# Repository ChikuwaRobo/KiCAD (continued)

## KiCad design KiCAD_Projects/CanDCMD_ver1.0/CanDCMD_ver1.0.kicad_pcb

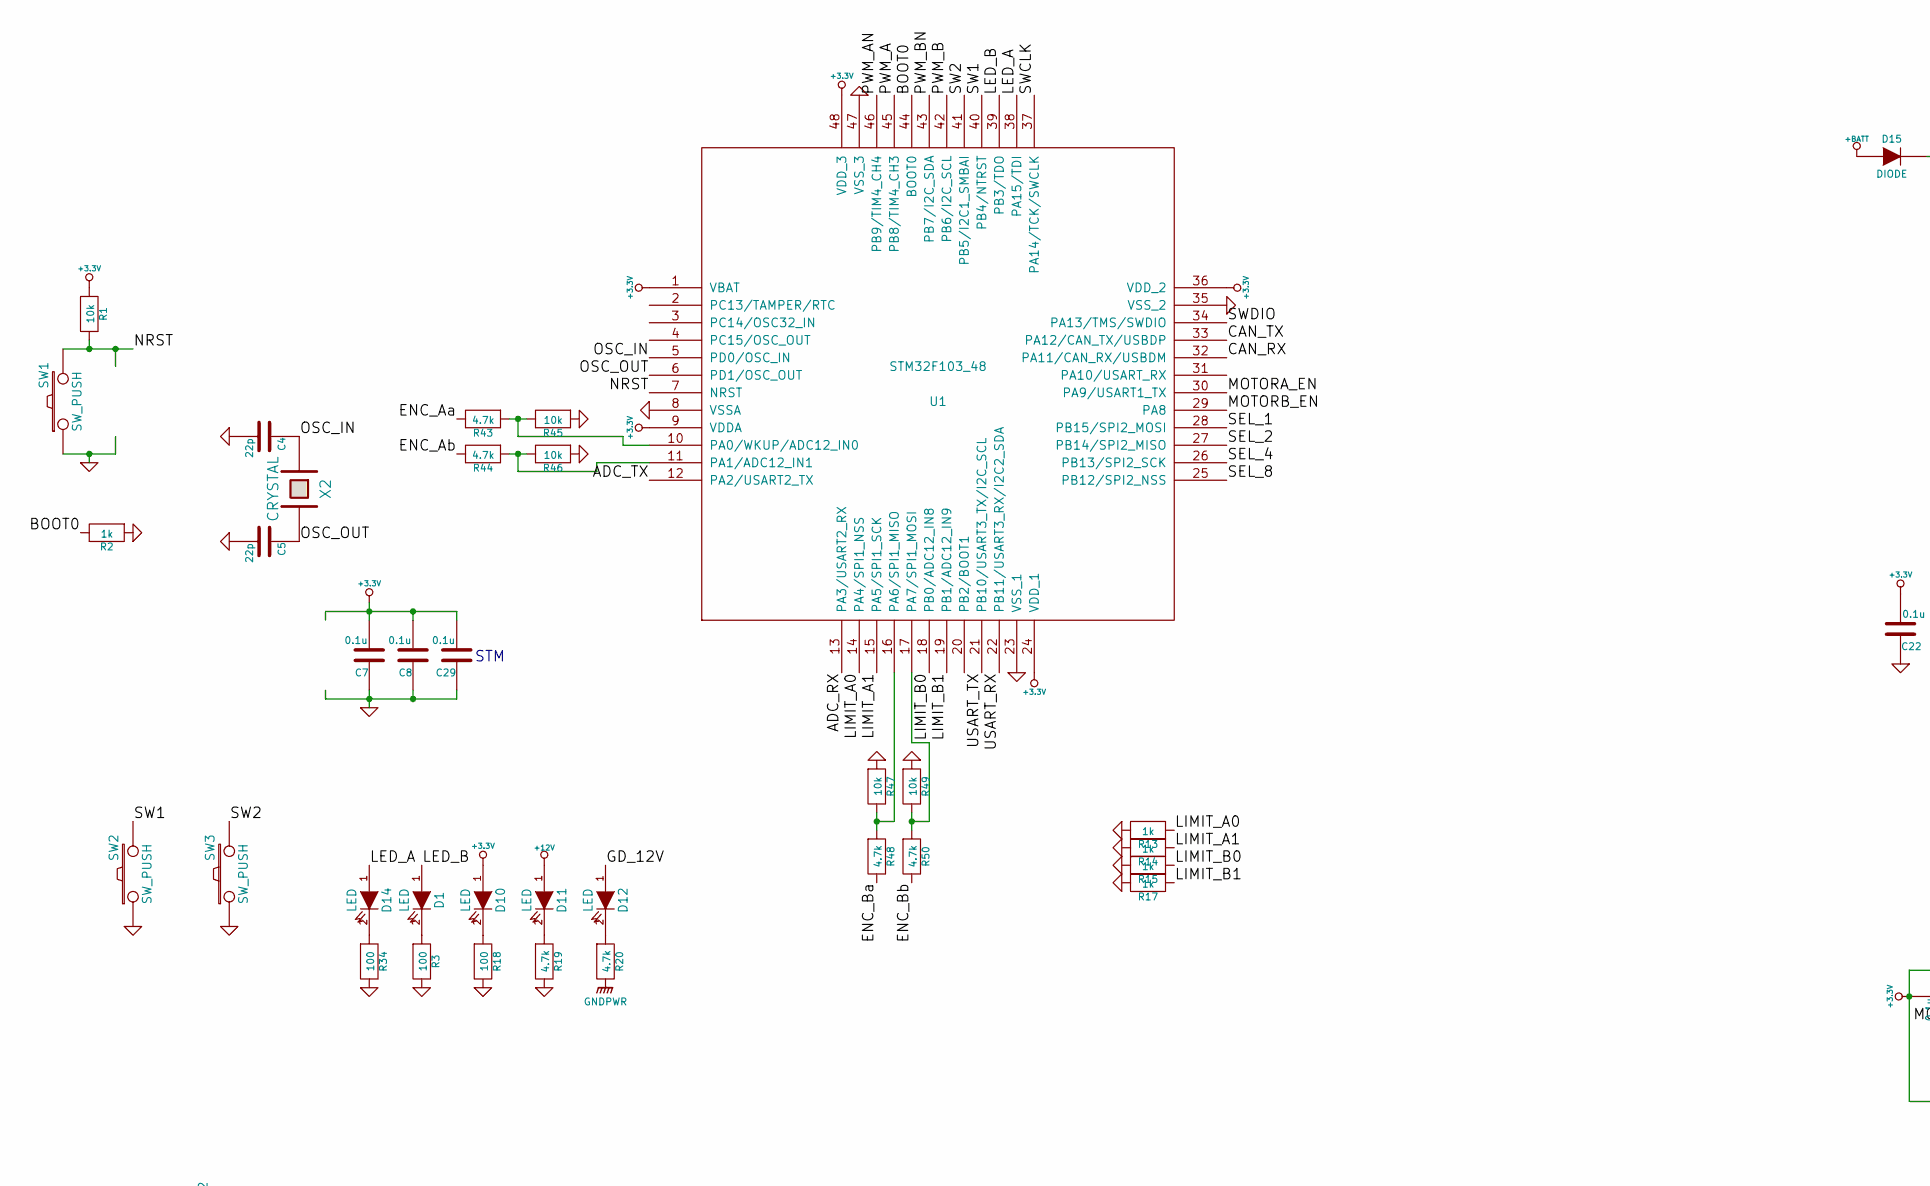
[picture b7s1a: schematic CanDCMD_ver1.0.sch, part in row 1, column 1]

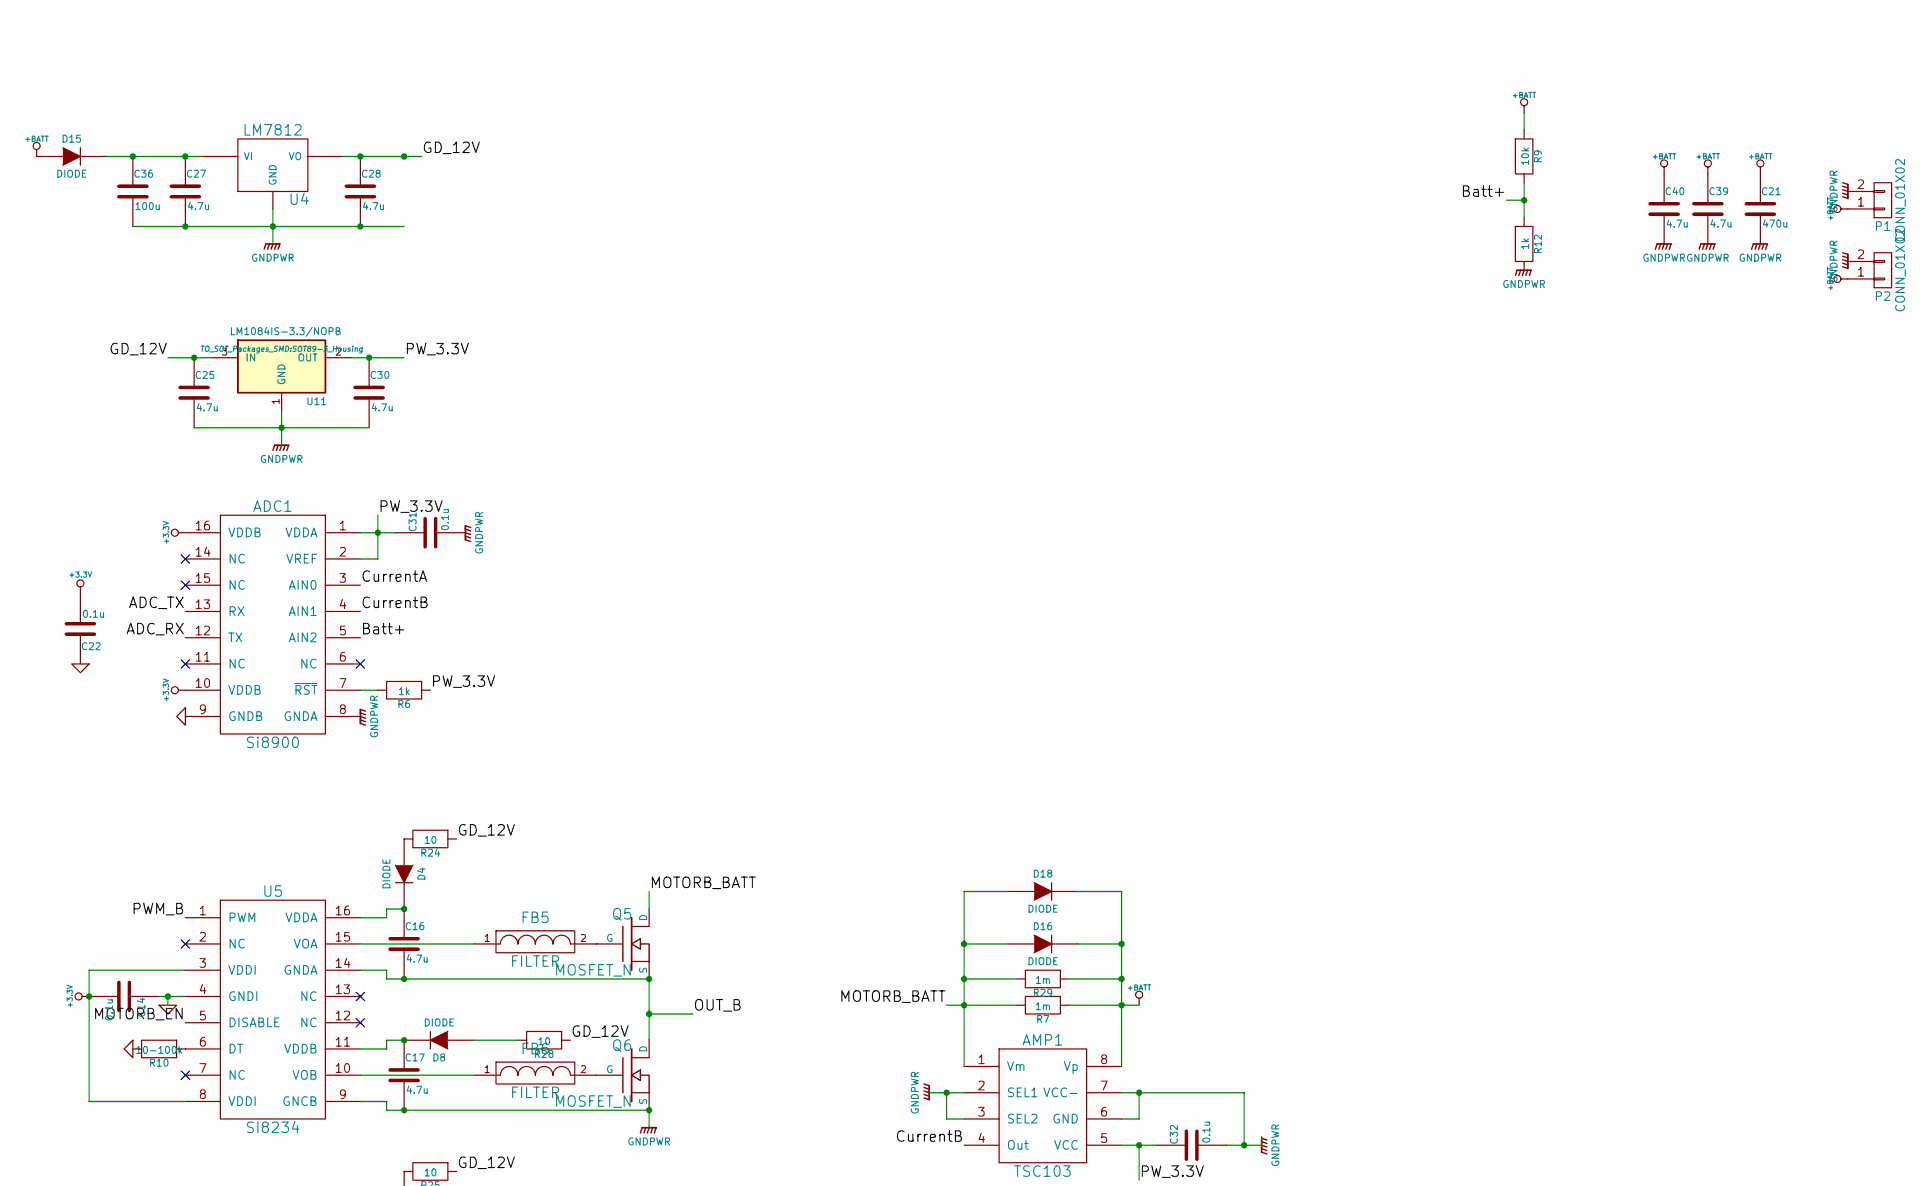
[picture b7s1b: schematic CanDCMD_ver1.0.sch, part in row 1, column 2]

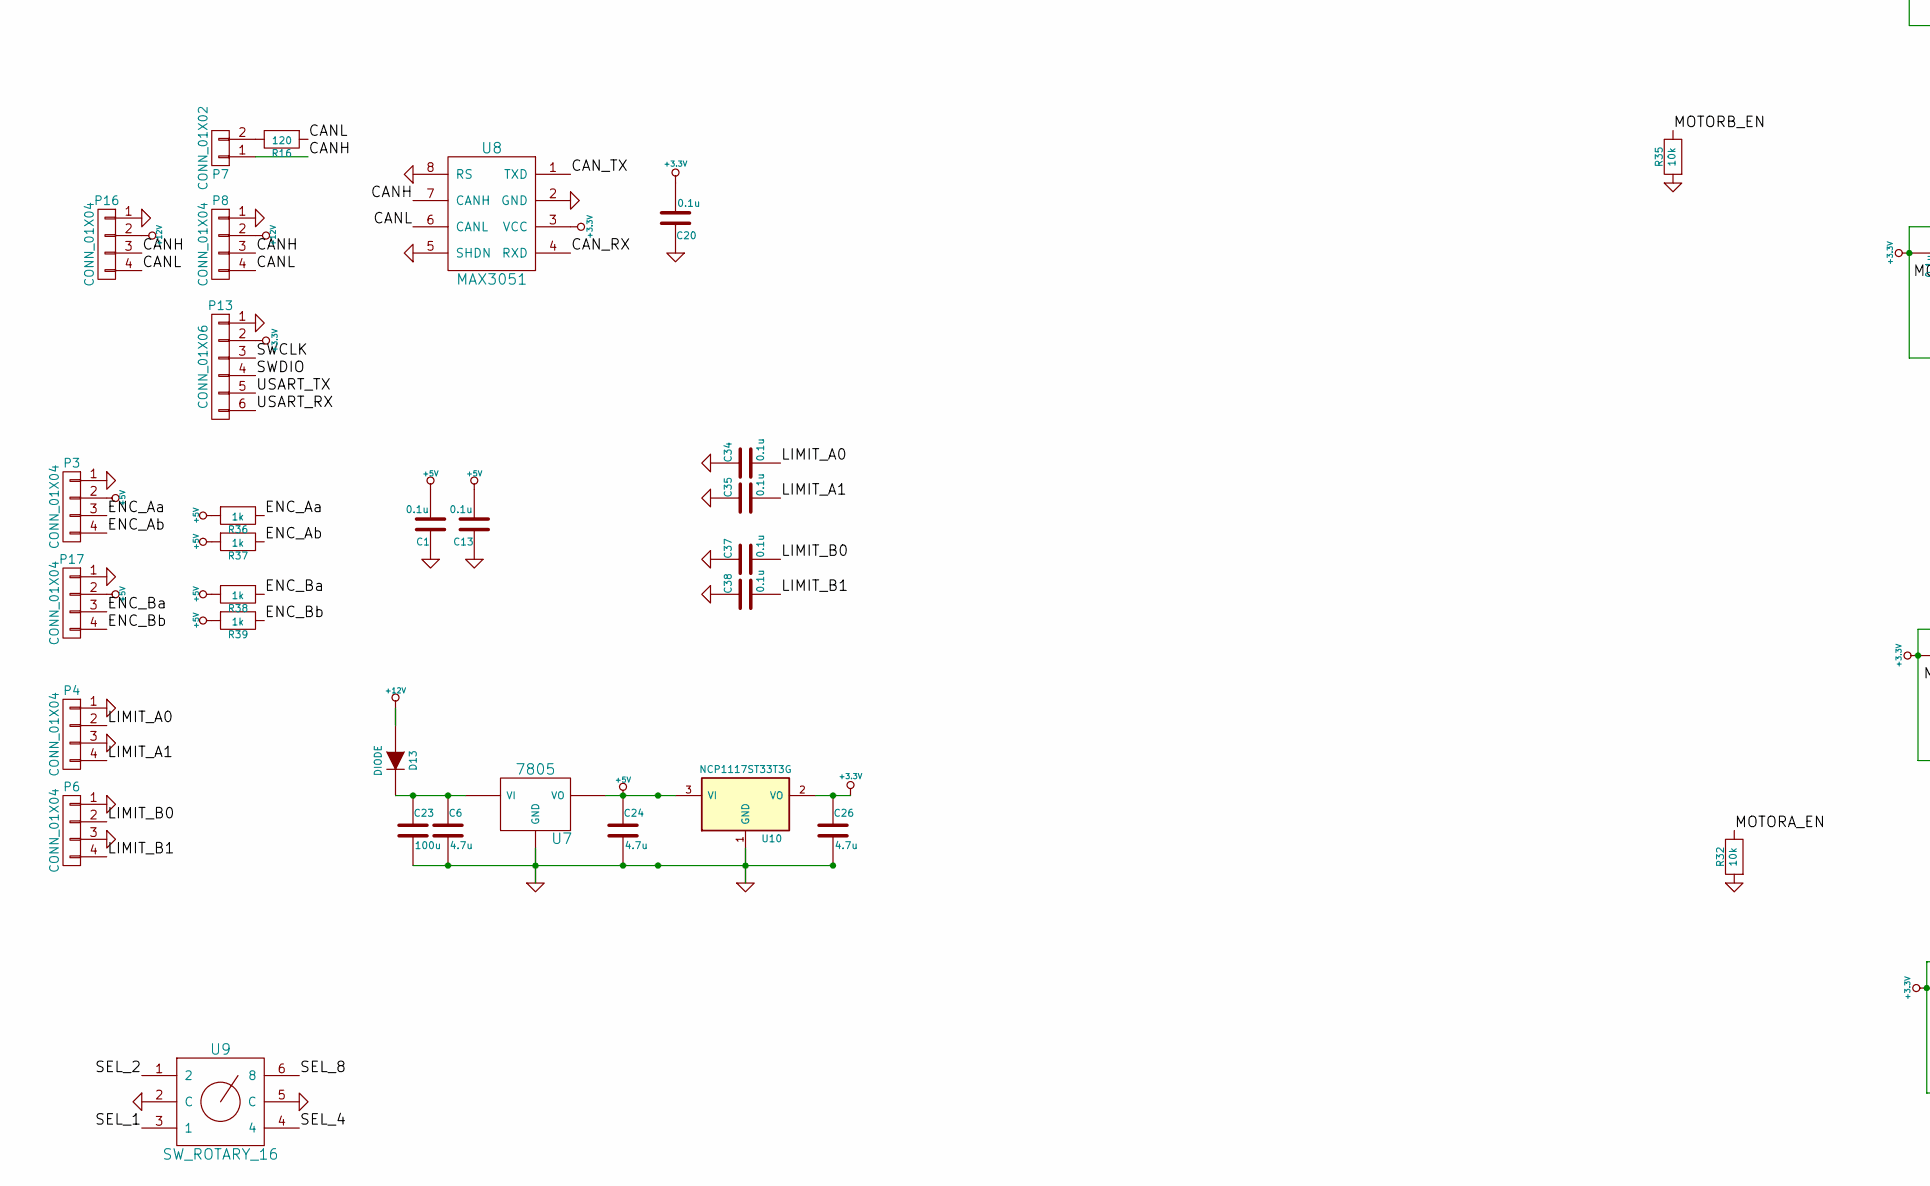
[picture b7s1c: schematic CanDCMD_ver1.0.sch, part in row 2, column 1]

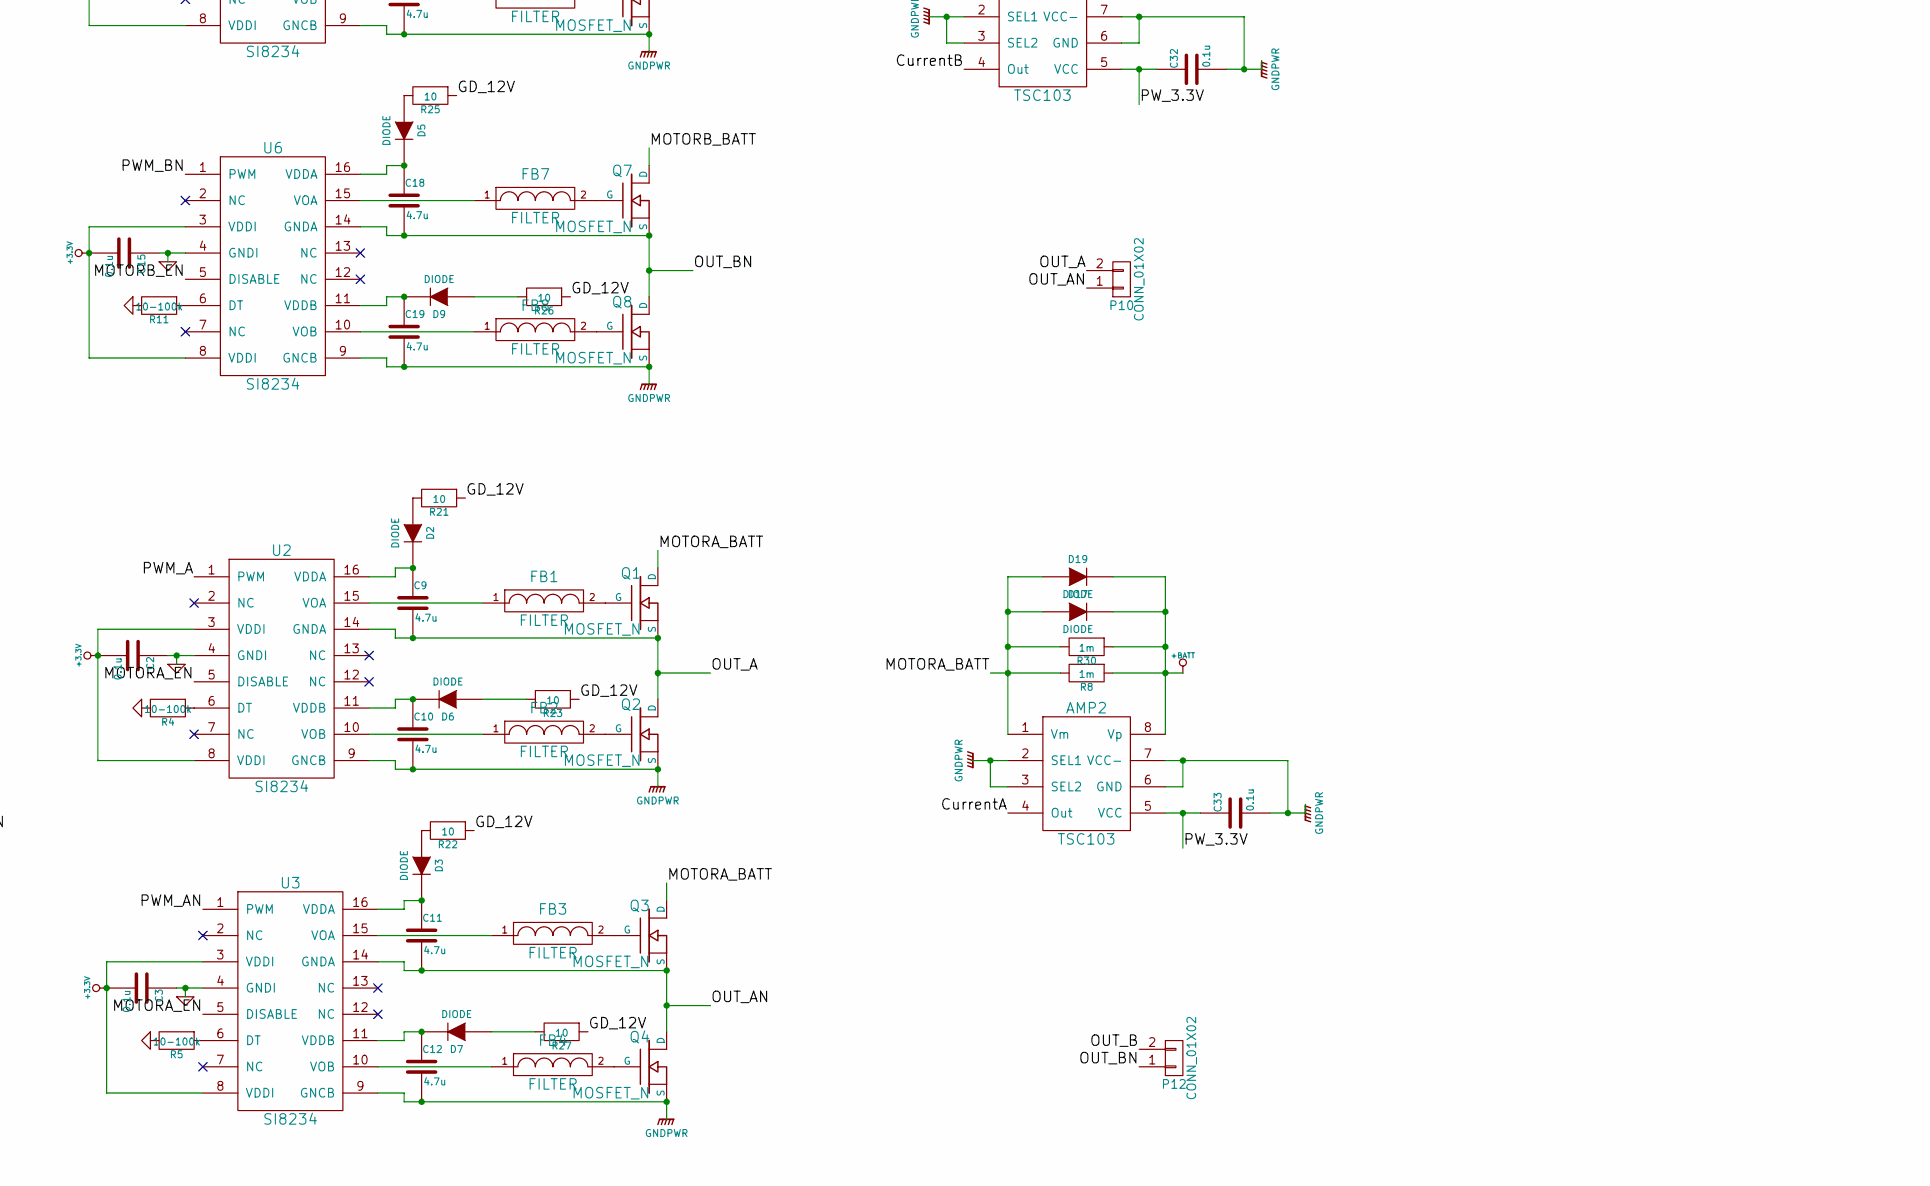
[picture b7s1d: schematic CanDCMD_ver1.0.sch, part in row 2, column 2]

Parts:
ADC1: Si8900; SOIC-16_7.5x10.3mm_Pitch1.27mm
AMP1, AMP2: TSC103; SOIC-8_3.9x4.9mm_Pitch1.27mm
C1, C2, C3, C7, C8, C13, C14, C15, C20, C22, C29, C31, C32, C33, C34, C35, C37, C38: 0.1u; C1608_WP
C4, C5: 22p; C1608_WP
C6, C9, C10, C11, C12, C16, C17, C18, C19, C24, C25, C26, C27, C28, C30, C39, C40: 4.7u; C3216
C21: 470u; C_Radial_D12.5_L25_P5
C23, C36: 100u; C_Radial_D6.3_L11.2_P2.5
D1, D10, D11, D12, D14: LED; C1608_WP
D2, D3, D4, D5, D6, D7, D8, D9: DIODE; C1608_WP
D13, D15: DIODE; C3216
D16, D17, D18, D19: DIODE; POWER_DI5
FB1, FB2, FB3, FB4, FB5, FB6, FB7, FB8: FILTER; C1608_WP
P1: CONN_01X02; DEANS_T_M
P2: CONN_01X02; DEANS_T_F
P3, P4, P6, P8, P16, P17: CONN_01X04; XA_4LC
P7: CONN_01X02; Pin_Header_Straight_1x02
P10, P12: CONN_01X02; DEANS_T_F_minPad
P13: CONN_01X06; ZH_6T
Q1, Q2, Q3, Q4, Q5, Q6, Q7, Q8: MOSFET_N; D2-PAK_compact
R1, R9, R32, R35, R45, R46, R47, R49: 10k; C1608_WP
R2, R6, R12, R13, R14, R15, R17, R36, R37, R38, R39: 1k; C1608_WP
R3, R18, R34: 100; C1608_WP
R4, R5, R10, R11: 10-100k; C1608_WP
R7, R8, R29, R30: 1m; R5025
R16: 120; C1608_WP
R19, R20, R43, R44, R48, R50: 4.7k; C1608_WP
R21, R22, R23, R24, R25, R26, R27, R28: 10; C1608_WP
SW1, SW2, SW3: SW_PUSH; RP_SMD_Button
U1: STM32F103_48; LQFP-48_7x7mm_Pitch0.5mm
U2, U3, U5, U6: SI8234; SOIC-16_3.9x9.9mm_Pitch1.27mm
U4: LM7812; TO-252-2Lead_regu
U7: 7805; TO-252-2Lead_regu
U8: MAX3051; SOIC-8_3.9x4.9mm_Pitch1.27mm
U9: SW_ROTARY_16; rotary_0F
U10: NCP1117ST33T3G; SOT-223_reg
U11: LM1084IS-3.3/NOPB; SOT89-3_Housing
X2: CRYSTAL; ABM3_2pads

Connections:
+3.3V: ADC1.10 (VDDB), ADC1.16 (VDDB), C2.2, C3.2, C7.2, C8.2, C14.2, C15.2, C20.2, C22.2, C26.1, C29.2, D10.1 (A), P13.2, R1.1, U1.1 (VBAT), U1.9 (VDDA), U1.24 (VDD_1), U1.36 (VDD_2), U1.48 (VDD_3), U2.3 (VDDI), U2.8 (VDDI), U3.3 (VDDI), U3.8 (VDDI), U5.3 (VDDI), U5.8 (VDDI), U6.3 (VDDI), U6.8 (VDDI), U8.3 (VCC), U10.2 (VO)
+5V: C1.2, C13.2, C24.1, P3.2, P17.2, R36.1, R37.1, R38.1, R39.1, U7.VO, U10.3 (VI)
+12V: D11.1 (A), D13.1 (A), P8.2, P16.2
+BATT: AMP1.8 (Vp), AMP2.8 (Vp), C21.1, C39.1, C40.1, D15.1 (A), D16.1 (K), D17.1 (K), D18.1 (K), D19.1 (K), P1.1, P2.1, R7.1, R8.1, R9.1, R29.1, R30.1
/ADC_RX: ADC1.12 (TX), U1.13 (PA3/USART2_RX)
/ADC_TX: ADC1.13 (RX), U1.12 (PA2/USART2_TX)
/BOOT0: R2.2, U1.44 (BOOT0)
/Batt+: ADC1.5 (AIN2), R9.2, R12.1
/CANH: P7.1, P8.3, P16.3, U8.7 (CANH)
/CANL: P8.4, P16.4, R16.1, U8.6 (CANL)
/CAN_RX: U1.32 (PA11/CAN_RX/USBDM), U8.4 (RXD)
/CAN_TX: U1.33 (PA12/CAN_TX/USBDP), U8.1 (TXD)
/CurrentA: ADC1.3 (AIN0), AMP2.4 (Out)
/CurrentB: ADC1.4 (AIN1), AMP1.4 (Out)
/ENC_Aa: P3.3, R36.2, R43.2
/ENC_Ab: P3.4, R37.2, R44.2
/ENC_Ba: P17.3, R38.2, R48.2
/ENC_Bb: P17.4, R39.2, R50.2
/GD_12V: C25.1, C28.1, D12.1 (A), R21.1, R22.1, R23.1, R24.1, R25.1, R26.1, R27.1, R28.1, U4.VO, U11.3 (IN)
/LED_A: D14.1 (A), U1.38 (PA15/TDI)
/LED_B: D1.1 (A), U1.39 (PB3/TDO)
/LIMIT_A0: C34.2, P4.2, R13.1, U1.14 (PA4/SPI1_NSS)
/LIMIT_A1: C35.2, P4.4, R14.1, U1.15 (PA5/SPI1_SCK)
/LIMIT_B0: C37.2, P6.2, R15.1, U1.18 (PB0/ADC12_IN8)
/LIMIT_B1: C38.2, P6.4, R17.1, U1.19 (PB1/ADC12_IN9)
/MOTORA_BATT: AMP2.1 (Vm), D17.2 (A), D19.2 (A), Q1.D, Q3.D, R8.2, R30.2
/MOTORA_EN: R32.2, U1.30 (PA9/USART1_TX), U2.5 (DISABLE), U3.5 (DISABLE)
/MOTORB_BATT: AMP1.1 (Vm), D16.2 (A), D18.2 (A), Q5.D, Q7.D, R7.2, R29.2
/MOTORB_EN: R35.2, U1.29 (PA8), U5.5 (DISABLE), U6.5 (DISABLE)
/NRST: R1.2, SW1.2, U1.7 (NRST)
/OSC_IN: C4.1, U1.5 (PD0/OSC_IN), X2.1
/OSC_OUT: C5.1, U1.6 (PD1/OSC_OUT), X2.2
/OUT_A: C9.2, P10.2, Q1.S, Q2.D, U2.14 (GNDA)
/OUT_AN: C11.2, P10.1, Q3.S, Q4.D, U3.14 (GNDA)
/OUT_B: C16.2, P12.2, Q5.S, Q6.D, U5.14 (GNDA)
/OUT_BN: C18.2, P12.1, Q7.S, Q8.D, U6.14 (GNDA)
/PWM_A: U1.45 (PB8/TIM4_CH3), U2.1 (PWM)
/PWM_AN: U1.46 (PB9/TIM4_CH4), U3.1 (PWM)
/PWM_B: U1.42 (PB6/I2C_SCL), U5.1 (PWM)
/PWM_BN: U1.43 (PB7/I2C_SDA), U6.1 (PWM)
/PW_3.3V: ADC1.1 (VDDA), ADC1.2 (VREF), AMP1.5 (VCC), AMP2.5 (VCC), C30.1, C31.1, C32.1, C33.1, R6.1, U11.2 (OUT)
/SEL_1: U1.28 (PB15/SPI2_MOSI), U9.3 (1)
/SEL_2: U1.27 (PB14/SPI2_MISO), U9.1 (2)
/SEL_4: U1.26 (PB13/SPI2_SCK), U9.4
/SEL_8: U1.25 (PB12/SPI2_NSS), U9.6 (8)
/SW1: SW2.2, U1.40 (PB4/NTRST)
/SW2: SW3.2, U1.41 (PB5/I2C1_SMBAI)
/SWCLK: P13.3, U1.37 (PA14/TCK/SWCLK)
/SWDIO: P13.4, U1.34 (PA13/TMS/SWDIO)
/USART_RX: P13.6, U1.22 (PB11/USART3_RX/I2C2_SDA)
/USART_TX: P13.5, U1.21 (PB10/USART3_TX/I2C_SCL)
GND: ADC1.9 (GNDB), C1.1, C2.1, C3.1, C4.2, C5.2, C6.2, C7.1, C8.1, C13.1, C14.1, C15.1, C20.1, C22.1, C23.2, C24.2, C26.2, C29.1, C34.1, C35.1, C37.1, C38.1, P3.1, P4.1, P4.3, P6.1, P6.3, P8.1, P13.1, P16.1, P17.1, R2.1, R3.2, R4.2, R5.2, R10.2, R11.2, R13.2, R14.2, R15.2, R17.2, R18.2, R19.2, R32.1, R34.2, R35.1, R45.1, R46.1, R47.1, R49.1, SW1.1, SW2.1, SW3.1, U1.8 (VSSA), U1.23 (VSS_1), U1.35 (VSS_2), U1.47 (VSS_3), U2.4 (GNDI), U3.4 (GNDI), U5.4 (GNDI), U6.4 (GNDI), U7.GND, U8.2 (GND), U8.5 (SHDN), U8.8 (RS), U9.2 (C), U9.5 (C), U10.1 (GND)
GNDPWR: ADC1.8 (GNDA), AMP1.2 (SEL1), AMP1.3 (SEL2), AMP1.6 (GND), AMP1.7 (VCC-), AMP2.2 (SEL1), AMP2.3 (SEL2), AMP2.6 (GND), AMP2.7 (VCC-), C10.2, C12.2, C17.2, C19.2, C21.2, C25.2, C27.2, C28.2, C30.2, C31.2, C32.2, C33.2, C36.2, C39.2, C40.2, P1.2, P2.2, Q2.S, Q4.S, Q6.S, Q8.S, R12.2, R20.2, U2.9 (GNCB), U3.9 (GNCB), U4.GND, U5.9 (GNCB), U6.9 (GNCB), U11.1 (GND)
unnamed: ADC1.7 (~RST), R6.2
unnamed: C9.1, D2.2 (K), U2.16 (VDDA)
unnamed: C10.1, D6.2 (K), U2.11 (VDDB)
unnamed: C11.1, D3.2 (K), U3.16 (VDDA)
unnamed: C12.1, D7.2 (K), U3.11 (VDDB)
unnamed: C16.1, D4.2 (K), U5.16 (VDDA)
unnamed: C17.1, D8.2 (K), U5.11 (VDDB)
unnamed: C18.1, D5.2 (K), U6.16 (VDDA)
unnamed: C19.1, D9.2 (K), U6.11 (VDDB)
unnamed: C6.1, C23.1, D13.2 (K), U7.VI
unnamed: C27.1, C36.1, D15.2 (K), U4.VI
unnamed: D1.2 (K), R3.1
unnamed: D2.1 (A), R21.2
unnamed: D3.1 (A), R22.2
unnamed: D4.1 (A), R24.2
unnamed: D5.1 (A), R25.2
unnamed: D6.1 (A), R23.2
unnamed: D7.1 (A), R27.2
unnamed: D8.1 (A), R28.2
unnamed: D9.1 (A), R26.2
unnamed: D10.2 (K), R18.1
unnamed: D11.2 (K), R19.1
unnamed: D12.2 (K), R20.1
unnamed: D14.2 (K), R34.1
unnamed: FB1.1, U2.15 (VOA)
unnamed: FB1.2, Q1.G
unnamed: FB2.1, U2.10 (VOB)
unnamed: FB2.2, Q2.G
unnamed: FB3.1, U3.15 (VOA)
unnamed: FB3.2, Q3.G
unnamed: FB4.1, U3.10 (VOB)
unnamed: FB4.2, Q4.G
unnamed: FB5.1, U5.15 (VOA)
unnamed: FB5.2, Q5.G
unnamed: FB6.1, U5.10 (VOB)
unnamed: FB6.2, Q6.G
unnamed: FB7.1, U6.15 (VOA)
unnamed: FB7.2, Q7.G
unnamed: FB8.1, U6.10 (VOB)
unnamed: FB8.2, Q8.G
unnamed: P7.2, R16.2
unnamed: R4.1, U2.6 (DT)
unnamed: R5.1, U3.6 (DT)
unnamed: R10.1, U5.6 (DT)
unnamed: R11.1, U6.6 (DT)
unnamed: R43.1, R45.2, U1.10 (PA0/WKUP/ADC12_IN0)
unnamed: R44.1, R46.2, U1.11 (PA1/ADC12_IN1)
unnamed: R47.2, R48.1, U1.16 (PA6/SPI1_MISO)
unnamed: R49.2, R50.1, U1.17 (PA7/SPI1_MOSI)

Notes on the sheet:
STM

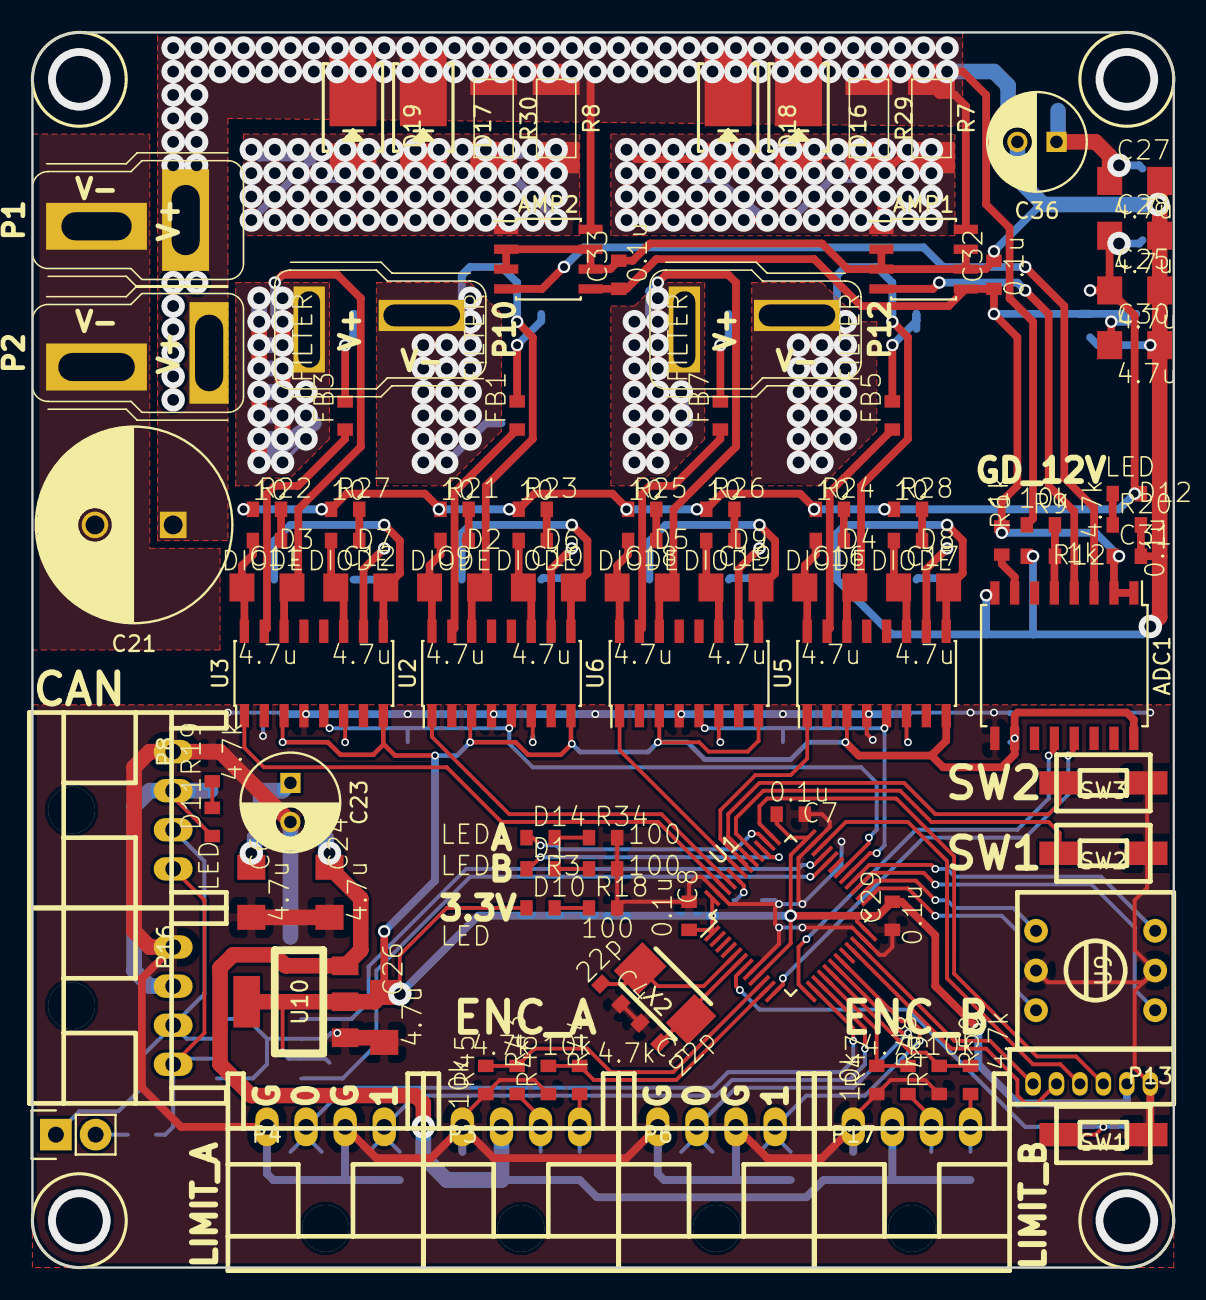
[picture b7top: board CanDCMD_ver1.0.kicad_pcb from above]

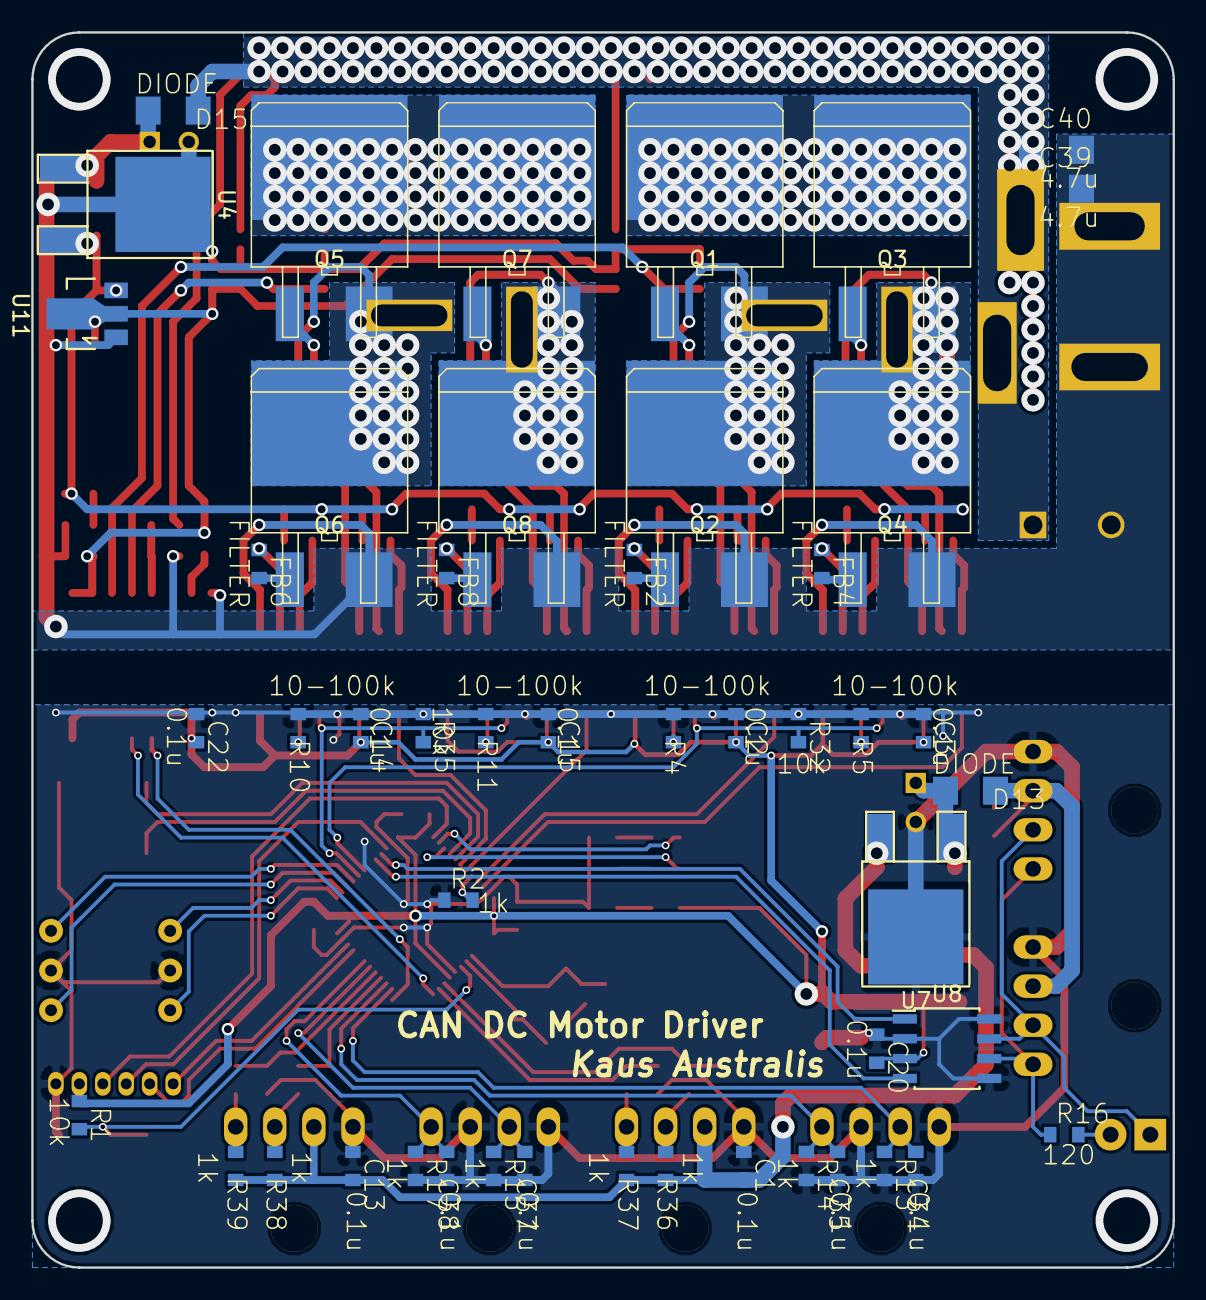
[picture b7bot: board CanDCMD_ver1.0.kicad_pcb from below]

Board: 2 copper layers, 73.0 x 79.0 mm, 150 parts (49 on the bottom side), 102 nets.
